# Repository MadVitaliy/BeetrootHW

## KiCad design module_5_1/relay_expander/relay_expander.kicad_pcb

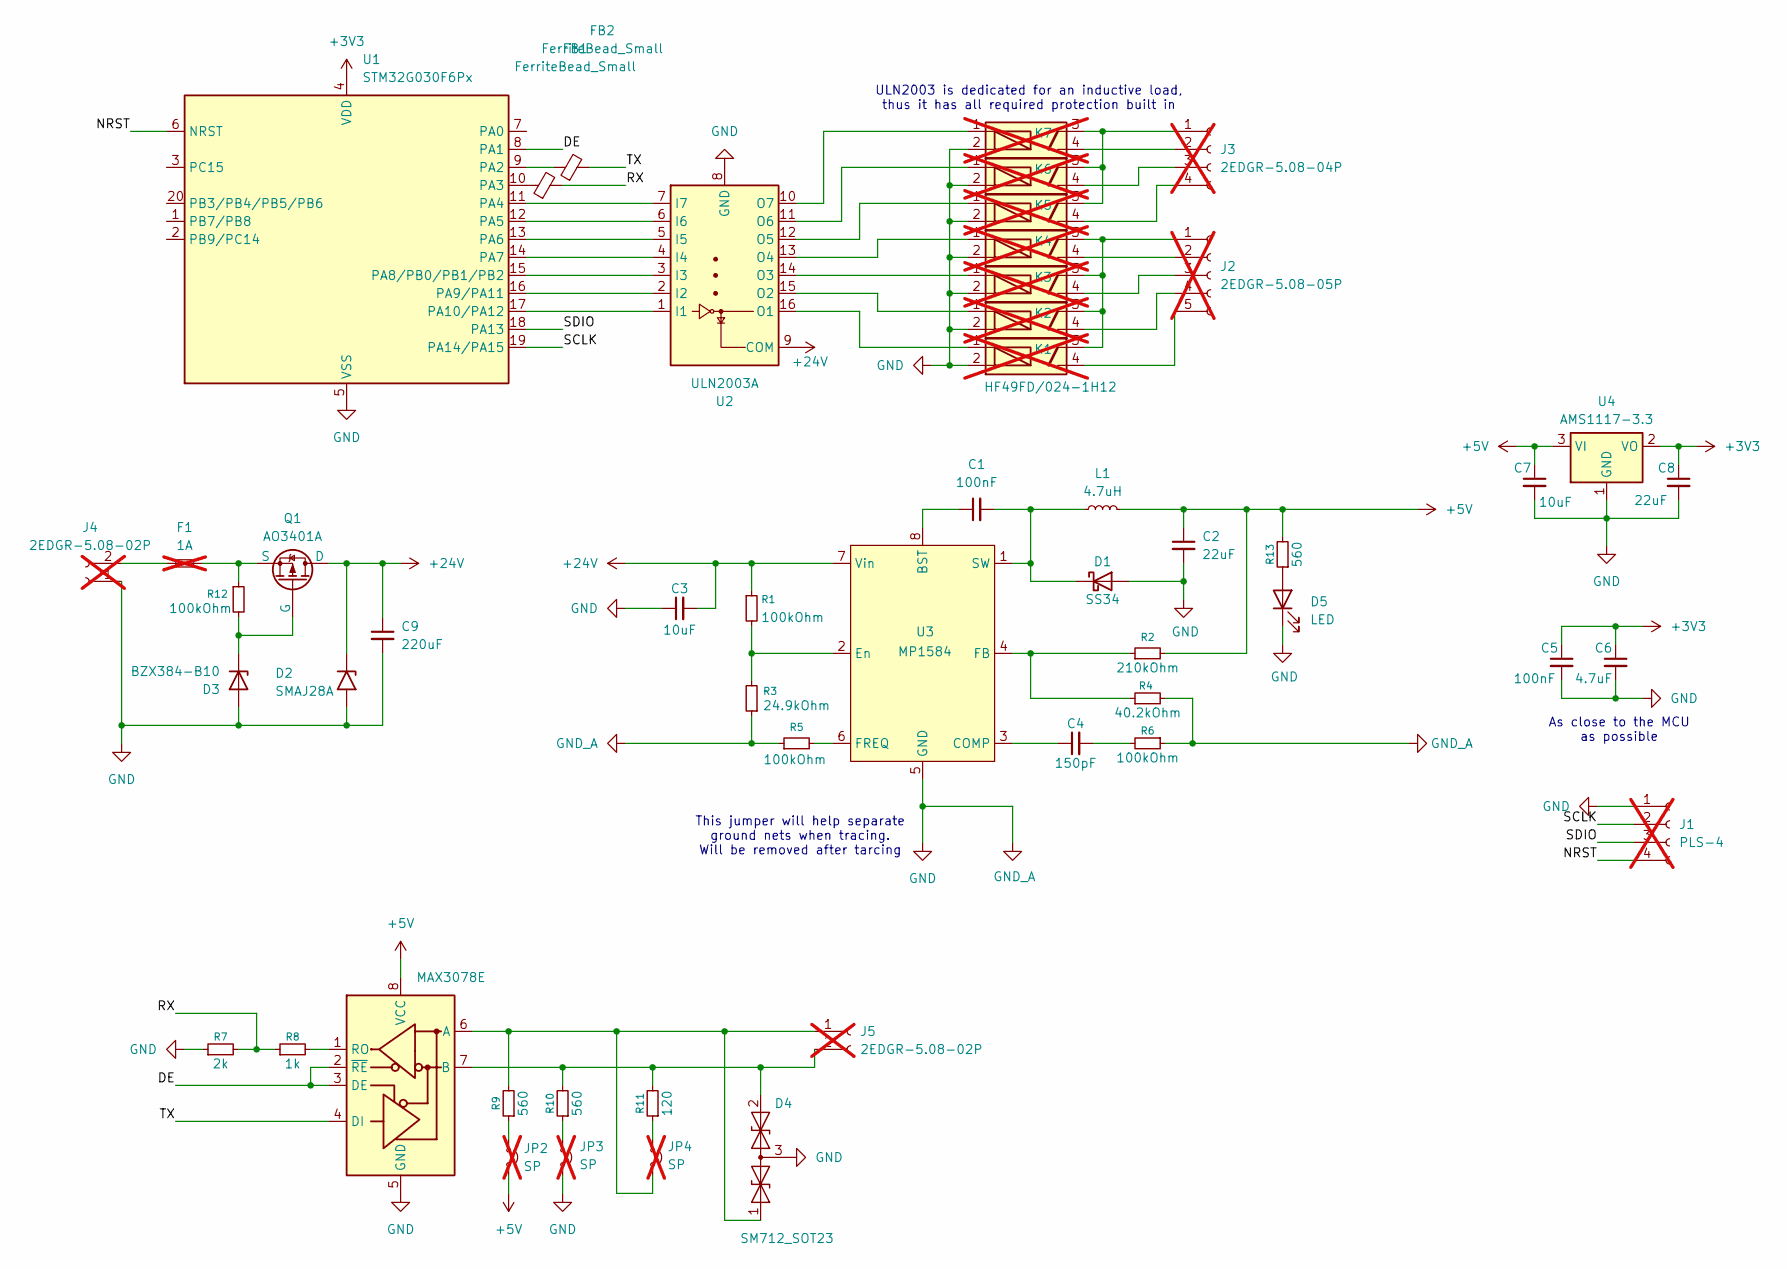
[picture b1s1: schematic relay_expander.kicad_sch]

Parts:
C1, C5: 100nF; C_0603_1608Metric_Pad1.08x0.95mm_HandSolder; MPN CL10B104JA8NNNC; LCSC Part C14663
C2, C8: 22uF; C_1206_3216Metric_Pad1.33x1.80mm_HandSolder; MPN CL31X476KQHNNNE; LCSC Part C12891
C3, C7: 10uF; C_1206_3216Metric_Pad1.33x1.80mm_HandSolder; MPN CL31B106KBHNNNE; LCSC Part C13585
C4: 150pF; C_0603_1608Metric_Pad1.08x0.95mm_HandSolder; MPN C1608C0G2E151J080AA; LCSC Part C14663
C6: 4.7uF; C_0603_1608Metric_Pad1.08x0.95mm_HandSolder; MPN CL10A475KP8NNNC; LCSC Part C19666
C9: 220uF; CP_Elec_8x10.5; MPN CS1V221M-CRF10; LCSC Part C3340
D1: SS34; D_SMA; MPN SS34; LCSC Part C8678
D2: SMAJ28A; D_SMA; MPN SMAJ28A-TR; LCSC Part C283899
D3: BZX384-B10; D_SOD-323; MPN BZX384-B10.115; LCSC Part C118044
D4: SM712_SOT23; SOT-23; MPN SM712; LCSC Part C32677
D5: LED; LED_0805_2012Metric_Pad1.15x1.40mm_HandSolder; MPN KT-SMD1206-G
F1: 1A; R_Axial_DIN0414_L11.9mm_D4.5mm_P15.24mm_Horizontal; MPN FUSE 1A 250V 3X10; not fitted
FB1, FB2: FerriteBead_Small; C_0805_2012Metric_Pad1.18x1.45mm_HandSolder; MPN BLM21AJ601SN1D; LCSC Part C1015
J1: PLS-4; PinHeader_1x04_P2.54mm_Vertical; MPN CL10B104JA8NNNC; not fitted
J2: 2EDGR-5.08-05P; MPN 2EDGR-5.08-05P-14-00AH; not fitted
J3: 2EDGR-5.08-04P; MPN 2EDGR-5.08-04P-14-00AH; not fitted
J4, J5: 2EDGR-5.08-02P; MPN 2EDGR-5.08-02P-14-00AH; not fitted
JP2, JP3, JP4: SP; SolderJumper-2_P1.3mm_Open_TrianglePad1.0x1.5mm; not fitted
K1, K2, K3, K4, K5, K6, K7: HF49FD/024-1H12; Relay_HF41F_24-HS_Vertical; MPN HF49FD/024-1H12; not fitted
L1: 4.7uH; L_Vishay_IHLP-2525; MPN SMD0650_4u7H; LCSC Part C182159
Q1: AO3401A; SOT-23-3; MPN AO3401A; LCSC Part C15127
R1, R5, R6, R12: 100kOhm; R_0603_1608Metric_Pad0.98x0.95mm_HandSolder; MPN RC0603FR-07100KL; LCSC Part C14675
R2: 210kOhm; R_0603_1608Metric_Pad0.98x0.95mm_HandSolder; MPN RC0805FR-210K-Hitano; LCSC Part C22952
R3: 24.9kOhm; R_0805_2012Metric_Pad1.20x1.40mm_HandSolder; MPN SMD 24.9K 0805 1%; LCSC Part C25962
R4: 40.2kOhm; R_0603_1608Metric_Pad0.98x0.95mm_HandSolder; MPN RC0603FR-40K2R-Hitano; LCSC Part C12447
R7: 2k; R_0603_1608Metric_Pad0.98x0.95mm_HandSolder; MPN RC0603FR-072KL; LCSC Part C22975
R8: 1k; R_0603_1608Metric_Pad0.98x0.95mm_HandSolder; MPN RC0603FR-071KL; LCSC Part C14676
R9, R10, R13: 560; R_0603_1608Metric_Pad0.98x0.95mm_HandSolder; MPN RC03K3561JT-KOME; LCSC Part C23204
R11: 120; R_0603_1608Metric_Pad0.98x0.95mm_HandSolder; MPN RC0603JR-07120RL; LCSC Part C22787
U1: STM32G030F6Px; TSSOP-20_4.4x6.5mm_P0.65mm; MPN STM32G030F6P6TR; LCSC Part C724040
U2: ULN2003A; SOIC-16_3.9x9.9mm_P1.27mm; MPN ULN2003ADR; LCSC Part C7512
U3: MP1584; SOIC-8_3.9x4.9mm_P1.27mm; MPN MP1584EN; LCSC Part C49367328
U4: AMS1117-3.3; SOT-223-3_TabPin2; MPN AMS1117-3.3; LCSC Part C6186
U5: MAX3078E; SOIC-8_3.9x4.9mm_P1.27mm; MPN SP485REN-L/TR; LCSC Part C12545

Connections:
+3V3: C5.1, C6.1, C8.1, U1.4 (VDD), U4.2 (VO)
+5V: C2.1, C7.1, JP2.2 (B), L1.2, R2.2, R13.2, U4.3 (VI), U5.8 (VCC)
+24V: C3.2, C9.1, D2.1 (A1), Q1.3 (D), R1.1, U2.9 (COM), U3.7 (Vin)
/DE: U1.8 (PA1), U5.2 (~RE), U5.3 (DE)
/NRST: J1.4, U1.6 (NRST)
/RX: FB1.2, R7.2, R8.1
/SCLK: J1.2, U1.19 (PA14/PA15)
/SDIO: J1.3, U1.18 (PA13)
/TX: FB2.2, U5.4 (DI)
GND: C2.2, C3.1, C5.2, C6.2, C7.2, C8.2, C9.2, D1.2 (A), D2.2 (A2), D3.2 (A), D4.3 (common), D5.1 (K), J1.1, J4.1, JP3.2 (B), K1.2, K2.2, K3.2, K4.2, K5.2, K6.2, K7.2, R3.1, R4.2, R5.1, R6.1, R7.1, U1.5 (VSS), U2.8 (GND), U3.5 (GND), U4.1 (GND), U5.5 (GND)
unnamed: C4.2, R6.2
unnamed: C1.2, D1.1 (K), L1.1, U3.1 (SW)
unnamed: D3.1 (K), Q1.1 (G), R12.2
unnamed: D4.1 (A1), J5.1, JP4.2 (B), R9.2, U5.6 (A)
unnamed: D4.2 (A2), J5.2, R10.2, R11.2, U5.7 (B)
unnamed: D5.2 (A), R13.1
unnamed: J2.1, K1.3, K2.3, K3.3, K4.3
unnamed: J2.2, K4.4
unnamed: J2.3, K3.4
unnamed: J2.4, K2.4
unnamed: J2.5, K1.4
unnamed: J3.1, K5.3, K6.3, K7.3
unnamed: J3.2, K7.4
unnamed: J3.3, K6.4
unnamed: J3.4, K5.4
unnamed: F1.1, J4.2
unnamed: JP2.1 (A), R9.1
unnamed: JP3.1 (A), R10.1
unnamed: JP4.1 (A), R11.1
unnamed: F1.2, Q1.2 (S), R12.1
unnamed: FB2.1, U1.9 (PA2)
unnamed: FB1.1, U1.10 (PA3)
unnamed: U1.11 (PA4), U2.7 (I7)
unnamed: U1.12 (PA5), U2.6 (I6)
unnamed: U1.13 (PA6), U2.5 (I5)
unnamed: U1.14 (PA7), U2.4 (I4)
unnamed: U1.15 (PA8/PB0/PB1/PB2), U2.3 (I3)
unnamed: U1.16 (PA9/PA11), U2.2 (I2)
unnamed: U1.17 (PA10/PA12), U2.1 (I1)
unnamed: K1.1, U2.16 (O1)
unnamed: K2.1, U2.15 (O2)
unnamed: K3.1, U2.14 (O3)
unnamed: K4.1, U2.13 (O4)
unnamed: K5.1, U2.12 (O5)
unnamed: K6.1, U2.11 (O6)
unnamed: K7.1, U2.10 (O7)
unnamed: C1.1, U3.8 (BST)
unnamed: C4.1, U3.3 (COMP)
unnamed: R1.2, R3.2, U3.2 (En)
unnamed: R2.1, R4.1, U3.4 (FB)
unnamed: R5.2, U3.6 (FREQ)
unnamed: R8.2, U5.1 (RO)

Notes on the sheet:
As close to the MCU as possible
This jumper will help separate ground nets when tracing. Will be removed after tarcing
ULN2003 is dedicated for an inductive load, thus it has all required protection built in

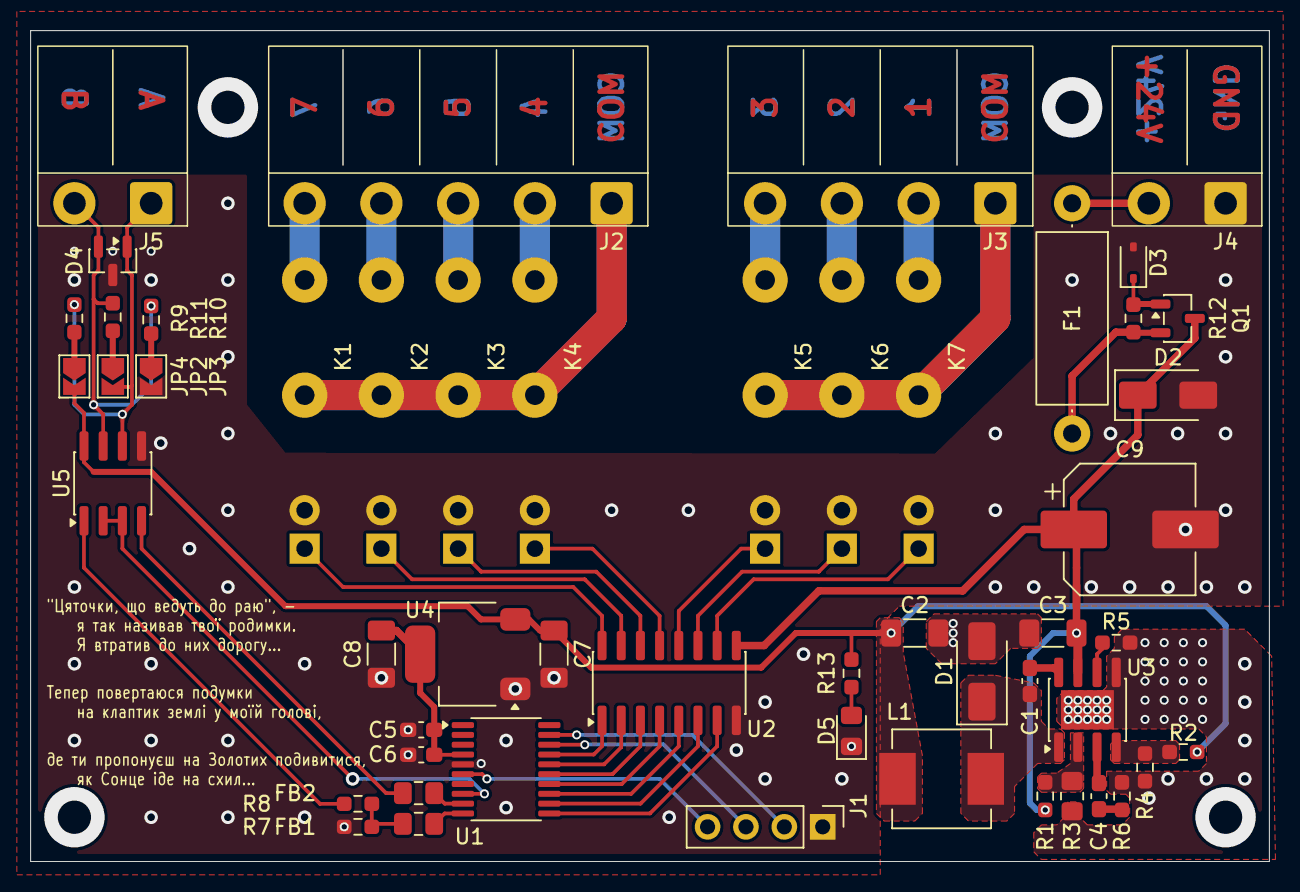
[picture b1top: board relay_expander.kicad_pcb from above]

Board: 2 copper layers, 82.0 x 55.0 mm, 52 parts (0 on the bottom side), 52 nets.

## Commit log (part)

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2026-04-06 gitignore has been added
2026-04-06 HW project has been added; it too late evening to write detailed description
2026-04-07 GPIO output states are changed via registers; Button has been added; Dummy debounce has been added as well;
2026-04-07 7-segment display based on a shift register (#1)
    * HW project has been added; it too late evening to write detailed description
    * GPIO output states are changed via registers;
    * Button has been added;
    * Dummy debounce has been added as well;
2026-04-07 * 7-segments display library has been moved to separate source files. * A raw button debounce library has been added.
2026-04-07 Forgot to add new files in the previous commit
2026-04-09 Newer vertion of button debug I like more; WasReleased and WasPressed functions have a flow of continious sending true
2026-04-09 Button debounce I like; 'WasPressed' and 'WasRelease' are triggered only once 'WasPressedFor' function are triggered only once as well
2026-04-18 Module 1.4 Button debounce (#2)
    * * 7-segments display library has been moved to separate source files.
    * A raw button debounce library has been added.
    * Forgot to add new files in the previous commit
    * Newer vertion of button debug I like more; WasReleased and WasPressed functions have a flow of continious sending true
    * Button debounce I like;
    'WasPressed' and 'WasRelease' are triggered only once
2026-04-18 *array buttons class has been added; it does not calculate ranges yet; *interrupt on the button pres to clear display;
2026-05-05 *array buttons class has been added; it does not calculate ranges yet; (#3)
    *interrupt on the button pres to clear display;
2026-05-05 Code for PWM motor control
2026-05-05 Mechanical relay delay has been measured
2026-05-06 Sparkling beauty of RTOS
2026-05-06 Autogenerated README files have been deleted for cleaner PR
2026-05-07 A new project has been initiallized
2026-05-07 timer based blinker has been implemented
2026-05-07 Blinker based on RTOS timers has been implemented
2026-05-07 A small clean up
2026-05-09 The HW task has been done using deep sleep and RTC wake ups.
2026-05-11 The first esp idf project. It builds, it flushes, it blinks.
    Let's add a potentiometer support.
2026-05-11 analogue reading and pwm generetion work(finally)
2026-05-12 ADC sampling and PWM controll have been seperated into tasks. Queue is used to pass data beetween tasks.
2026-05-12 Multithreading (finally!)
2026-05-12 The project has been recreated via expample template to fix static analysator scope. It goes smother with it.
2026-05-12 * SPI ram was anabled * defines has been replaced with constexpr variables * a tiny clean * minimal build was enabled * required components were added (in cmake)
2026-05-12 *stack sizes have been reduced for the tasks *the queue size has been reduced to 1, because I want to use just the last read value
2026-05-14 cores attachments have been fixed
2026-05-21 A draft of stopwatch done with espidf framework. Event based approach has been used. The current workflow diagram looks like:
    1. A button triggers an external intterups.
    2. Button's intterups ISR saves a current timestamp, disable the button interrupt and queues a high priority task to run a one shot timer.
    3. The timer task runs the one shot timer.
    4. When the timer is hit, its callback check a stable button state and enable the button interrupt again. The callback run or suspend the stopwatch depends on button's state.
2026-05-21 Project folder has been renamed
